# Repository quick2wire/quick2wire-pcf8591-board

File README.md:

# PCF8591 8-bit A/D and D/A expansion board

This is an simple expansion board for [nxp](http://www.nxp.com/)'s [PCF8591](http://www.nxp.com/documents/data_sheet/PCF8591.pdf) 8-bit A/D and D/A converter.

-------------------------------------------------------
Copyright (c) 2013 Quick2Wire Ltd. http://quick2wire.com

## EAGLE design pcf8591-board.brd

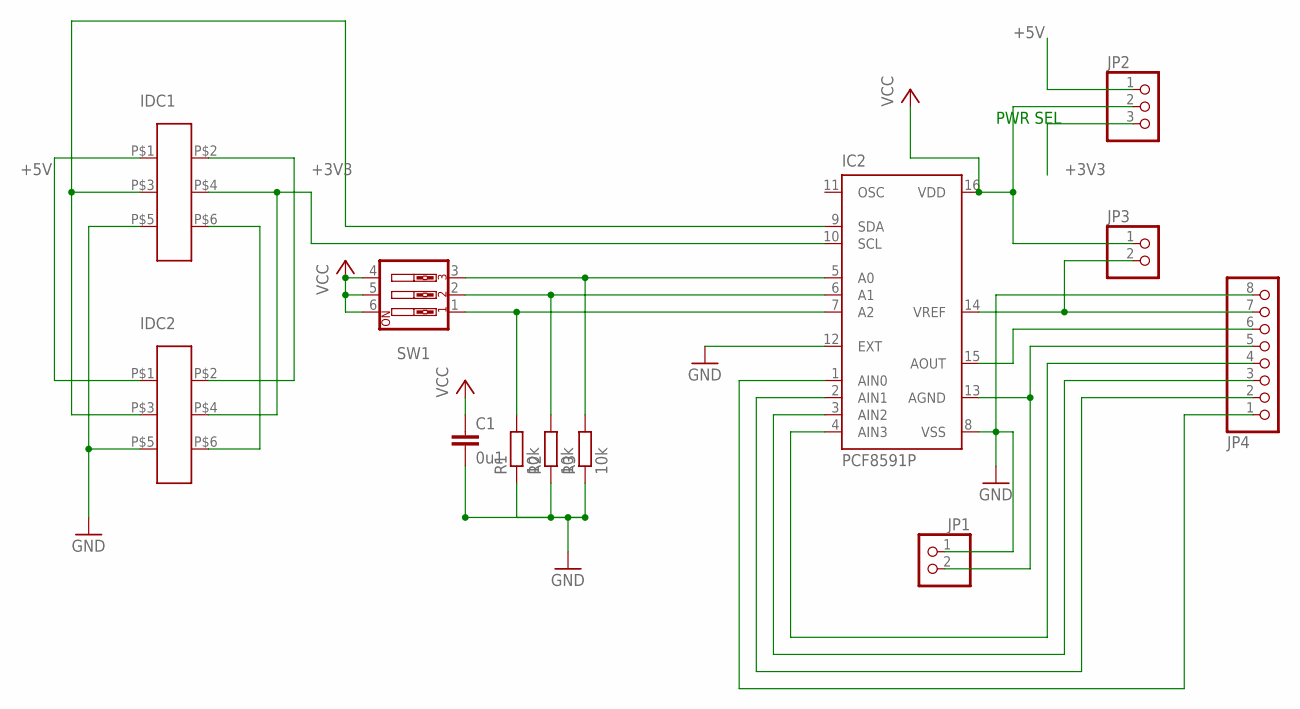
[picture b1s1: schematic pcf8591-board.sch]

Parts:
C1: 0u1; C025-030X050
IC2: PCF8591P; DIL16
IDC1, IDC2: IDC-6W
JP1, JP3: PINHD-1X2; 1X02
JP2: PINHD-1X3; 1X03
JP4: PINHD-1X8; 1X08
R1, R2, R3: 10k; 0204/7
SW1: SW_DIP-3; EDG-03

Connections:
+3V3: IDC1.P$2, IDC2.P$2, JP2.3
+5V: IDC1.P$1, IDC2.P$1, JP2.1
A0: IC2.7 (A2), R1.2, SW1.1
A1: IC2.6 (A1), R2.2, SW1.2
A2: IC2.5 (A0), R3.2, SW1.3
GND: C1.2, IC2.8 (VSS), IC2.12 (EXT), IDC1.P$5, IDC2.P$5, JP1.1, JP4.8, R1.1, R2.1, R3.1
unnamed: IC2.1 (AIN0), JP4.1
unnamed: IC2.2 (AIN1), JP4.2
unnamed: IC2.3 (AIN2), JP4.3
unnamed: IC2.4 (AIN3), JP4.4
unnamed: IC2.13 (AGND), JP1.2, JP4.5
unnamed: IC2.15 (AOUT), JP4.6
unnamed: IC2.14 (VREF), JP3.2, JP4.7
unnamed: IDC1.P$6, IDC2.P$6
SCL: IC2.10 (SCL), IDC1.P$4, IDC2.P$4
SDA: IC2.9 (SDA), IDC1.P$3, IDC2.P$3
VCC: C1.1, IC2.16 (VDD), JP2.2, JP3.1, SW1.4, SW1.5, SW1.6

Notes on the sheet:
PWR SEL

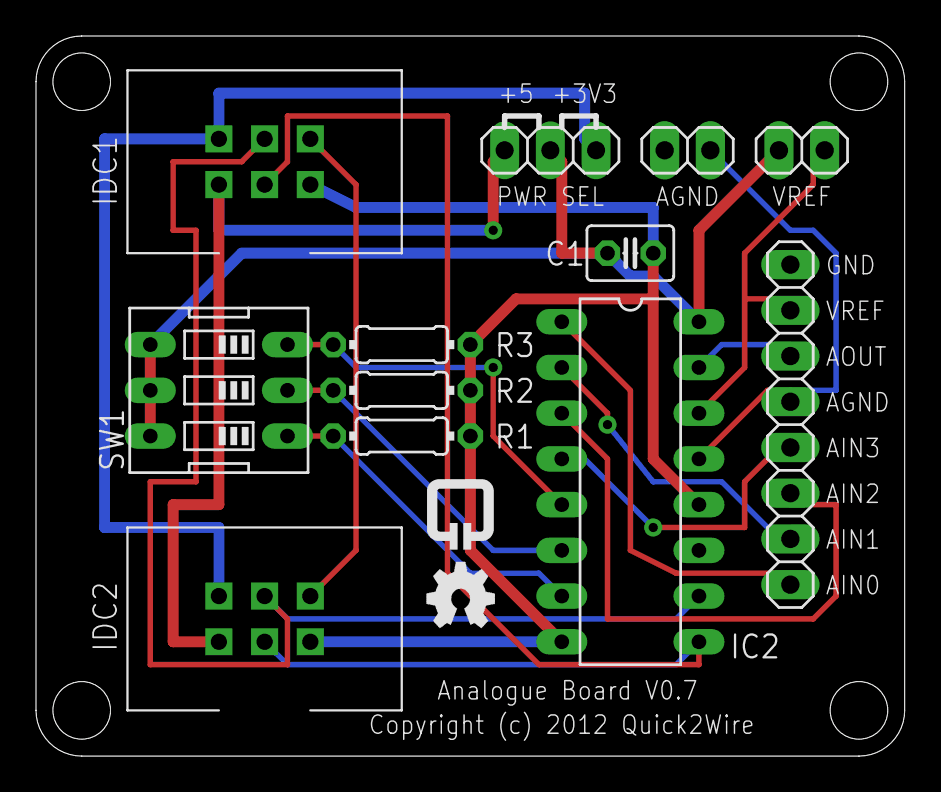
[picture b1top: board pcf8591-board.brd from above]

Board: 2 copper layers, 48.3 x 40.0 mm, 14 parts (0 on the bottom side), 17 nets.

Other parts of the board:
U$1: QUICK2WIRE-LOGO
U$2: OSHW-LOGO

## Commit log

2013-01-23 publishing version 0.4
2013-01-23 publishing version 0.5
2013-01-27 publishing version 0.7

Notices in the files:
pcf8591-board.brd:
Copyright (c) 2012 Quick2Wire
